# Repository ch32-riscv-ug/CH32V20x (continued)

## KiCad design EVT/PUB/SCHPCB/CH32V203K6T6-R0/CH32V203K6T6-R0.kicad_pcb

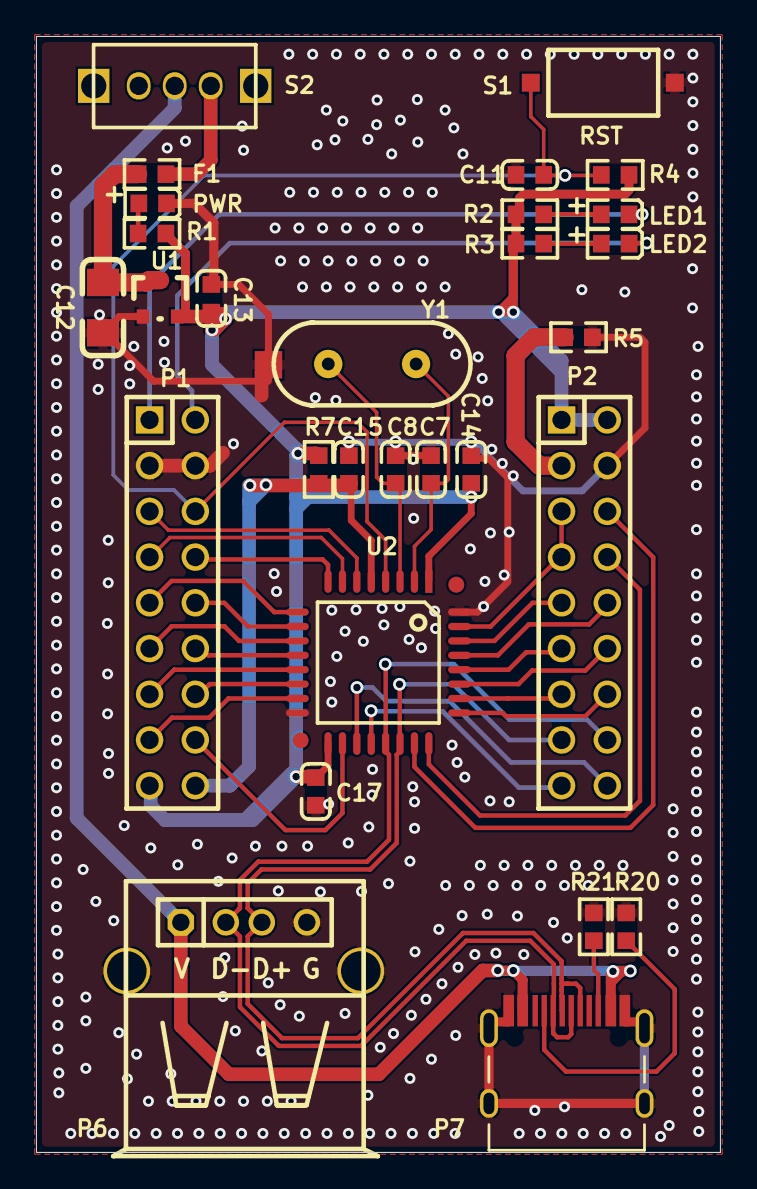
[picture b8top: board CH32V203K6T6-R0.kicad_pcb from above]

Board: 2 copper layers, 38.0 x 62.0 mm, 29 parts (0 on the bottom side), 41 nets.

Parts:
C7, C8: 22pF; 0603_C
C11, C14, C15, C17: 0.1uF; 0603_C
C12: 10uF; 3216_C
C13: 2.2uF; 0603_C
F1: 500mA; 0603
LED1: LED1 blue; 0603+
LED2: LED2 blue; 0603+
P1, P2: HEADER 9x2; IDC18-2.54MM
P6: USB_A; USBAF
P7: TYPE-C; TYPE-C-Receptacle-2.0
PWR: POWER red; 0603+
R1, R2, R3: 1K; 0603
R4: NC(10K); 0603
R5: 4.7K; 0603
R7: 0Ω; 0603
R20, R21: NC(5.1K); 0603
S1: RST; SMD_6.1x3.65x2.5mm-KEY
S2: SW; KEY2
U1: 6219P33M; SOT-23
U2: CH32V203K; LQFP32
Y1: 8M; XT_AT49

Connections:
+5V: P6.1, P7.A4, P7.B4, S2.1
BOOT0: P2.5, P2.7, U2.31
GND: C7.1, C8.1, C11.1, C12.2, C13.1, C14.1, C15.2, C17.2, P1.3, P1.4, P2.4, P6.0, P6.4, P7.0, P7.A1, P7.B1, PWR.2, R5.1, R20.2, R21.2, S1.2, U1.1, U2.16, U2.32, Y1.0
LED1: LED1.2, P1.1
LED2: LED2.2, P1.2
NRST: C11.2, P1.6, R4.1, S1.1, U2.4
NetC12_1: C12.1, F1.2, U1.3
NetF1_1: F1.1, S2.3
NetLED1_1: LED1.1, R2.2
NetLED2_1: LED2.1, R3.2
NetP2_3: P2.3, R5.2
NetP7_A5: P7.A5, R20.1
NetP7_B5: P7.B5, R21.1
NetPWR_1: PWR.1, R1.1
PA0: P1.5, U2.6
PA1: P1.7, U2.7
PA2: P1.8, U2.8
PA3: P1.9, U2.9
PA4: P1.10, U2.10
PA5: P1.11, U2.11
PA6: P1.12, U2.12
PA7: P1.13, U2.13
PA8: P1.16, U2.18
PA9: P2.18, U2.19
PA10: P2.17, U2.20
PA11: P2.16, P6.2, P7.A7, P7.B7, U2.21
PA12: P2.15, P6.3, P7.A6, P7.B6, U2.22
PA13: P2.6, U2.23
PA14: P2.8, U2.24
PA15: P2.14, U2.25
PB0: P1.14, U2.14
PB1: P1.15, U2.15
PB3: P2.13, U2.26
PB4: P2.12, U2.27
PB5: P2.11, U2.28
PB6: P2.10, U2.29
PB7: P2.9, U2.30
PD0: C7.2, U2.2, Y1.2
PD1: C8.2, U2.3, Y1.1
VCC: C13.2, C14.2, C17.1, P1.17, P2.1, P2.2, R1.2, R2.1, R3.1, R4.2, R7.1, U1.2, U2.1, U2.17
VDDA: C15.1, P1.18, R7.2, U2.5

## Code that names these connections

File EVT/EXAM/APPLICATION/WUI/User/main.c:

/*********************************************************************
 * File Name          : main.c
 * Author             : WCH
 * Version            : V1.0.0
 * Date               : 2026/08/06
 * Description        : Main program body.
 *********************************************************************************
* Copyright (c) 2023 Nanjing Qinheng Microelectronics Co., Ltd.
* Attention: This software (modified or not) and binary are used for 
* microcontroller manufactured by Nanjing Qinheng Microelectronics.
*******************************************************************************/

/*
 *@Note
 A demo for wui
  pins: 
    FLASH_CS   -- PA4
    FLASH_DO   -- PA6
    FLASH_DI   -- PA7
    FLASH_CLK  -- PA5
    
    LCD_LED    -- PB9
    LCD_DC     -- PB10
    LCD_RST    -- PB11
    LCD_CS     -- PB12
    LCD_SCK    -- PB13
    LCD_MOSI   -- PB15


 */


#include <math.h>
#include "debug.h"
#include "string.h"
#include "lcd.h"
#include "flash.h"
#include "config.h"
#include "wui.h"
#include "wui_port.h"
#include "wui_user/wui_page.h"

/* Global define */

/* Global Variable */


#define TIM_PCK (8000ul)

/*********************************************************************
 * @fn      TIM4_init
 *
 * @brief   Initialize TIM2 for WCHGUI
 *        
 * @return  none.
 */
void TIM4_init()
{
    RCC_APB1PeriphClockCmd(RCC_APB1Periph_TIM4, ENABLE);

    TIM_TimeBaseInitTypeDef TIM_TimeBaseInitStructure = {0};

    TIM_Cmd(TIM4, DISABLE);

    TIM_TimeBaseInitStructure.TIM_Period        = 0xffff;
    TIM_TimeBaseInitStructure.TIM_Prescaler     = ((SystemCoreClock) / TIM_PCK) - 1;
    TIM_TimeBaseInitStructure.TIM_ClockDivision = TIM_CKD_DIV1;
    TIM_TimeBaseInitStructure.TIM_CounterMode   = TIM_CounterMode_Up;
    TIM_TimeBaseInit(TIM4, &TIM_TimeBaseInitStructure);

    TIM_ARRPreloadConfig(TIM4, DISABLE);
    TIM_ClearFlag(TIM4, TIM_FLAG_Update);

    TIM_Cmd(TIM4, ENABLE);
}

/*********************************************************************
 * @fn      TIM3_Encoder_Init
 *
 * @brief   Initialize TIM1 for encoder
 *        
 * @return  none.
 */
void TIM3_Encoder_Init()
{
    TIM_TimeBaseInitTypeDef TIM_TimeBaseStructure;
    TIM_ICInitTypeDef       TIM_ICInitStructure;
    GPIO_InitTypeDef        GPIO_InitStructure = {0};

    RCC_APB2PeriphClockCmd(RCC_APB2Periph_GPIOA, ENABLE);
    RCC_APB1PeriphClockCmd(RCC_APB1Periph_TIM3, ENABLE);
    RCC_APB2PeriphClockCmd(RCC_APB2Periph_AFIO, ENABLE);
    RCC_APB2PeriphClockCmd(RCC_APB2Periph_GPIOB, ENABLE);

    {
        GPIO_PinRemapConfig(GPIO_PartialRemap_TIM3, ENABLE);
        GPIO_InitStructure.GPIO_Pin  = GPIO_Pin_4 | GPIO_Pin_5;
        GPIO_InitStructure.GPIO_Mode = GPIO_Mode_IN_FLOATING;
        GPIO_Init(GPIOB, &GPIO_InitStructure);
    }

    TIM_TimeBaseStructInit(&TIM_TimeBaseStructure);
    TIM_TimeBaseStructure.TIM_Prescaler     = 0x0;
    TIM_TimeBaseStructure.TIM_Period        = 160;
    TIM_TimeBaseStructure.TIM_ClockDivision = TIM_CKD_DIV1;
    TIM_TimeBaseStructure.TIM_CounterMode   = TIM_CounterMode_Up;
    TIM_TimeBaseInit(TIM3, &TIM_TimeBaseStructure);

    TIM_EncoderInterfaceConfig(TIM3, TIM_EncoderMode_TI12, TIM_ICPolarity_Rising, TIM_ICPolarity_Rising);

    TIM_ICStructInit(&TIM_ICInitStructure);
    TIM_ICInitStructure.TIM_ICFilter = 10;
    TIM_ICInit(TIM3, &TIM_ICInitStructure);

    TIM_SetCounter(TIM3, 0);
    TIM_Cmd(TIM3, ENABLE);
}

/*********************************************************************
 * @fn      check_direction
 *
 * @brief    Compute the absolute value of a signed 32-bit integer.
 *        
 * @param   a Signed 32-bit integer.
 *
 * @return  Absolute value of a 
 */
uint32_t static inline iabs(int32_t a)
{
    if (a < 0)
    {
        return -a;
    }
    return a;
}

/*********************************************************************
 * @fn      check_direction
 *
 * @brief   Detect the rotation direction of the encoder
 *        
 * @param   current_value The current count value
 *
 * @return  direction The direction of the encoder's rotation
 */
int32_t check_direction(int current_value)
{

    static int last_value = 0;

    if (current_value == last_value)
    {
        return 0;
    }

    int diff = current_value - last_value;
    if (iabs(diff) < 4)
    {
        return 0;
    }

    int32_t direction;

    if (iabs(diff) < 80)
    {
        if (diff > 0)
        {
            direction = 1;
        }
        else
        {
            direction = -1;
        }
    }
    else
    {
        if (diff > 0)
        {
            direction = -1;
        }
        else
        {
            direction = 1;
        }
    }

    last_value = current_value;
    return direction;
}

#define ENC_KEY_PORT GPIOA
#define ENC_KEY_PIN  (GPIO_Pin_15)

#define ENC_KEY()    ((ENC_KEY_PORT->INDR & ENC_KEY_PIN) == 0)

uint32_t key3_state = 0;
/*********************************************************************
 * @fn      Key_GPIOInit
 *
 * @brief   Initialization of the key pins of the encoder
 *        
 * @return  none.
 */
void Key_GPIOInit(void)
{

    GPIO_InitTypeDef GPIO_InitStructure = {0};

    GPIO_InitStructure.GPIO_Pin  = ENC_KEY_PIN;
    GPIO_InitStructure.GPIO_Mode = GPIO_Mode_IPU;
    GPIO_Init(ENC_KEY_PORT, &GPIO_InitStructure);
}

static uint8_t wui_heap_buffer[4 * 1024];

/*********************************************************************
 * @fn      main
 *
 * @brief   Main program.
 *
 * @return  none
 */
int main(void)
{

    SystemCoreClockUpdate();
    Delay_Init();
    USART_Printf_Init(115200);
    printf("SystemClk:%d\r\n", SystemCoreClock);
    printf(__TIME__ "\n");

    SPI_FLASH_Init();

    uint32_t id = SPI_Flash_ReadJedecDeviceID();
    printf("flash_id %x\n", id);

    LCD_Init();

    TIM3_Encoder_Init();
    TIM4_init();
    Key_GPIOInit();

    wui_init_data_t data = {
        .page_count = WUI_PAGE_COUNT,
        .width      = LCD_WIDTH,
        .height     = LCD_HEIGHT,
        .heap_addr  = wui_heap_buffer,
        .heap_size  = sizeof(wui_heap_buffer),
    };

    wui_init(&data);

    wui_register_hal(wui_get_hal());

    wui_page_switch(WUI_START_PAGE);

    while (1)
    {

        uint16_t now = TIM4->CNT;
        if (now > 16)
        {
            now       = now / 8;
            TIM4->CNT = 0;

            wui_page_ui_tick(now);
        }

        wui_page_ui_update();
        uint32_t tcnt = TIM3->CNT;

        int32_t dir = check_direction(tcnt);

        if (dir > 0)
        {
            HW_Key_event('a');
        }
        else if (dir < 0)
        {
            HW_Key_event('d');
        }

        uint32_t k3 = ENC_KEY();
        if (k3)
        {
            if (key3_state)
            {
            }
            else
            {
                key3_state = 1;
                HW_Key_event('b');
            }
        }
        else
        {
            key3_state = 0;
        }
    }

    while (1)
    {
    }
}

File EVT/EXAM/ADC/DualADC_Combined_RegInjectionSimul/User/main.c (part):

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/*
 *@Note
 *dual ADC combined regular + injection + simultaneous sampling routine:
 *Rule group ADC1 channel 1 (PA1), ADC2 channel 4 (PA4), injection group ADC1
 *channel 3 (PA3) ADC2 channel 5 (PA5))
 *The rule group injection groups are all triggered by software, and the dual ADC
 *rule group data is obtained through the DMA interrupt, and the dual ADC injection
 *group data is obtained through the ADC interrupt.
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
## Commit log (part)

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2026-06-15 update update.sh and add GitHub Actions workflow for automated datasheet downloads
2026-06-15 update cron schedule for automated datasheet downloads to reduce server load
2026-06-15 refactor update job to simplify commit logic in GitHub Actions workflow
2026-06-16 update GitHub Actions schedule
2026-06-16 update (automated)
2026-06-19 update GitHub Actions workflow to implement keepalive logic and remove unnecessary permissions
2026-06-19 refactor fetch function in update.sh to simplify error handling and remove retry logic

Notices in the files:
EVT/EXAM/ADC/DualADC_Combined_RegInjectionSimul/User/main.c:
Copyright (c) 2021 Nanjing Qinheng Microelectronics Co., Ltd.
